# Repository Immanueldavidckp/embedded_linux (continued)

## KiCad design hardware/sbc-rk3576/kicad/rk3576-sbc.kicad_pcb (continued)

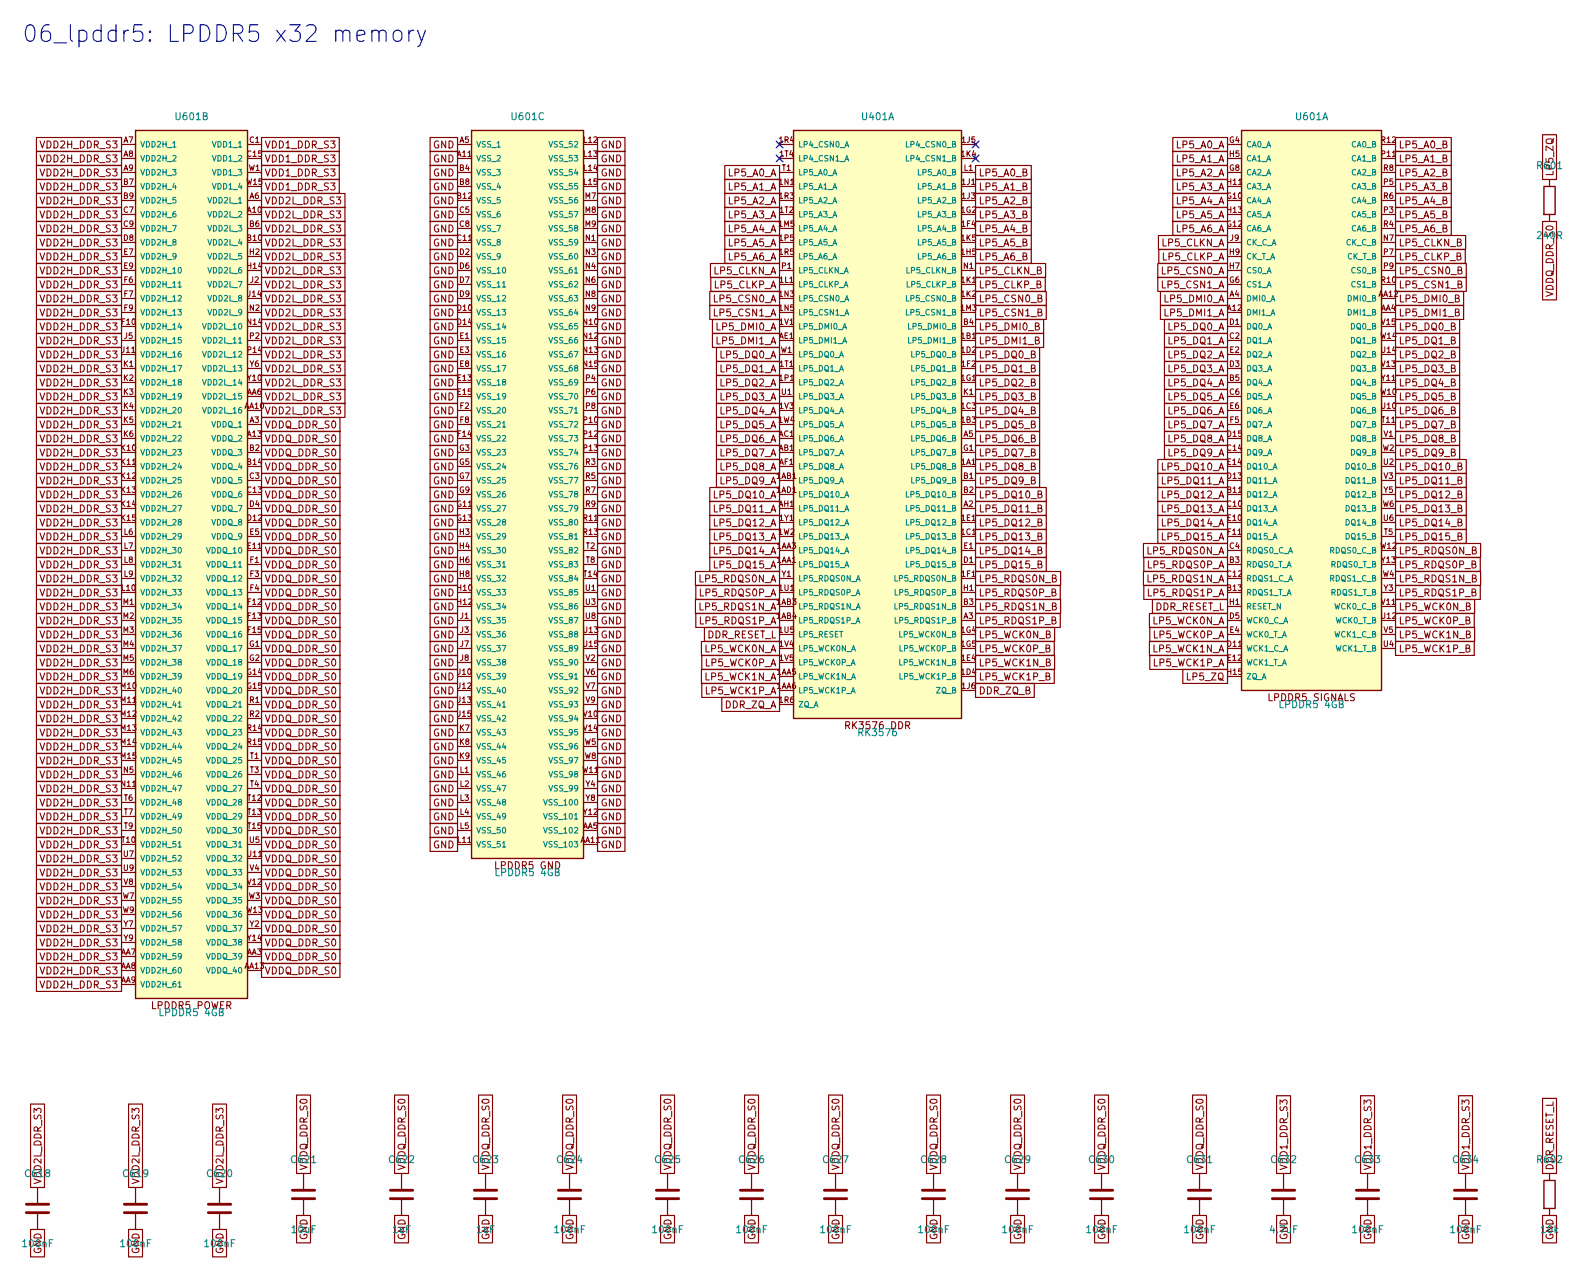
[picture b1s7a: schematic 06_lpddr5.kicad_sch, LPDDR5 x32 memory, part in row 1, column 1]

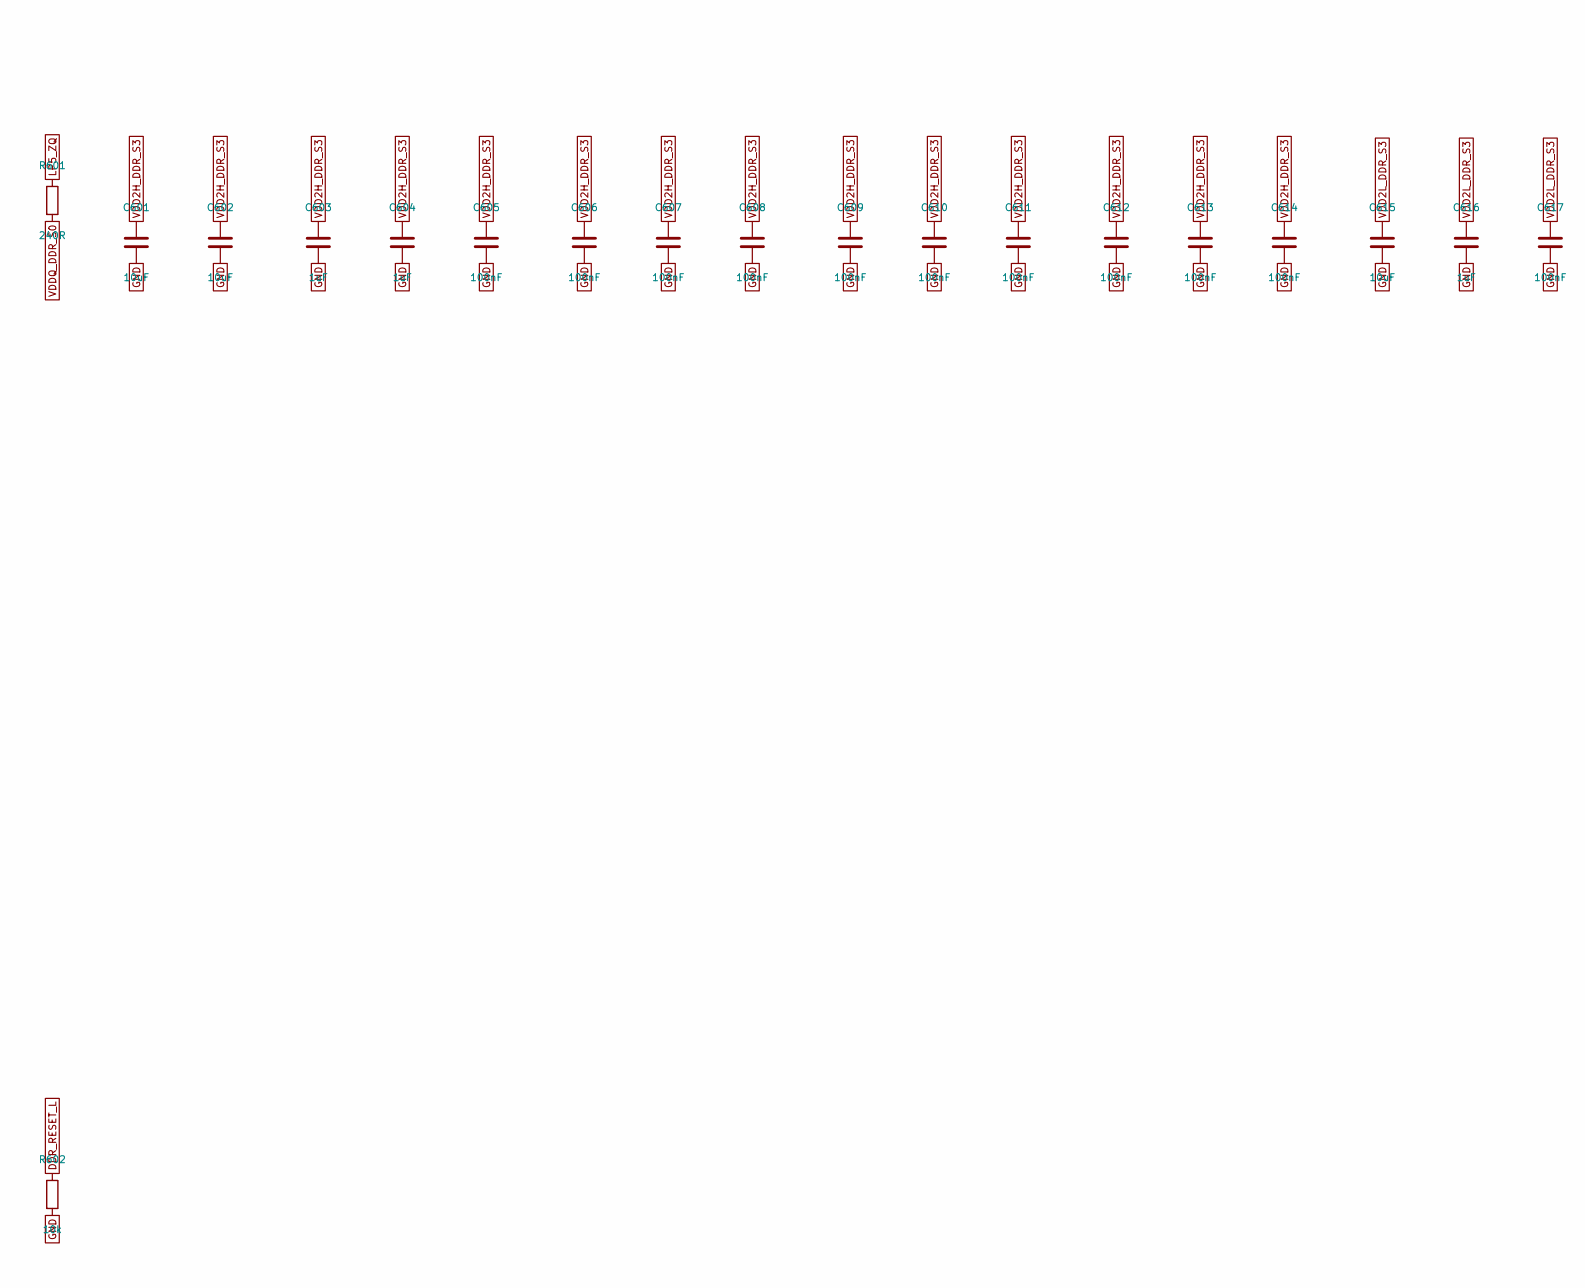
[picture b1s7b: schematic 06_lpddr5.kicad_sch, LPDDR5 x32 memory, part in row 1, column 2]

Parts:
C601, C602, C615, C621: 10uF; C_0603_1608Metric; MPN 0603 10uF 10V X5R
C603, C604, C616, C622, C623: 1uF; C_0402_1005Metric; MPN 0402 1uF 6.3V X5R
C605, C606, C607, C608, C609, C610, C611, C612, C613, C614, C617, C618, C619, C620, C624, C625, C626, C627, C628, C629, C630, C631, C633, C634: 100nF; C_0402_1005Metric; MPN 0402 100nF 6.3V X5R
C632: 4.7uF; C_0402_1005Metric; MPN 0402 4.7uF 10V X5R
R601: 240R; R_0402_1005Metric; MPN 0402 240R 1%
R602: 10k; R_0402_1005Metric; MPN 0402 10k 1%
U401: RK3576; RK3576_FCCSP-698_16.1x17.2mm; MPN RK3576
U601: LPDDR5 4GB; LPDDR5_FBGA-315_12.4x15.0mm_P0.8x0.7mm; MPN MT62F1G32D2DS-026 WT:B (4GB) | alt MT62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

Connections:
DDR_RESET_L: R602.1, U401.1U5 (LP5_RESET), U601.H1 (RESET_N)
DDR_ZQ_A: U401.1R6 (ZQ_A); also elsewhere on the board
DDR_ZQ_B: U401.1J6 (ZQ_B); also elsewhere on the board
GND: C601.2, C602.2, C603.2, C604.2, C605.2, C606.2, C607.2, C608.2, C609.2, C610.2, C611.2, C612.2, C613.2, C614.2, C615.2, C616.2, C617.2, C618.2, C619.2, C620.2, C621.2, C622.2, C623.2, C624.2, C625.2, C626.2, C627.2, C628.2, C629.2, C630.2, C631.2, C632.2, C633.2, C634.2, R602.2, U601.A5 (VSS_1), U601.A11 (VSS_2), U601.AA5 (VSS_102), U601.AA11 (VSS_103), U601.B4 (VSS_3), U601.B8 (VSS_4), U601.B12 (VSS_5), U601.C5 (VSS_6), U601.C8 (VSS_7), U601.C11 (VSS_8), U601.D2 (VSS_9), U601.D6 (VSS_10), U601.D7 (VSS_11), U601.D9 (VSS_12), U601.D10 (VSS_13), U601.D14 (VSS_14), U601.E1 (VSS_15), U601.E3 (VSS_16), U601.E8 (VSS_17), U601.E13 (VSS_18), U601.E15 (VSS_19), U601.F2 (VSS_20), U601.F8 (VSS_21), U601.F14 (VSS_22), U601.G3 (VSS_23), U601.G5 (VSS_24), U601.G7 (VSS_25), U601.G9 (VSS_26), U601.G11 (VSS_27), U601.G13 (VSS_28), U601.H3 (VSS_29), U601.H4 (VSS_30), U601.H6 (VSS_31), U601.H8 (VSS_32), U601.H10 (VSS_33), U601.H12 (VSS_34), U601.J1 (VSS_35), U601.J3 (VSS_36), U601.J7 (VSS_37), U601.J8 (VSS_38), U601.J10 (VSS_39), U601.J12 (VSS_40), U601.J13 (VSS_41), U601.J15 (VSS_42), U601.K7 (VSS_43), U601.K8 (VSS_44), U601.K9 (VSS_45), U601.L1 (VSS_46), U601.L2 (VSS_47), U601.L3 (VSS_48), U601.L4 (VSS_49), U601.L5 (VSS_50), U601.L11 (VSS_51), U601.L12 (VSS_52), U601.L13 (VSS_53), U601.L14 (VSS_54), U601.L15 (VSS_55), U601.M7 (VSS_56), U601.M8 (VSS_57), U601.M9 (VSS_58), U601.N1 (VSS_59), U601.N3 (VSS_60), U601.N4 (VSS_61), U601.N6 (VSS_62), U601.N8 (VSS_63), U601.N9 (VSS_64), U601.N10 (VSS_65), U601.N12 (VSS_66), U601.N13 (VSS_67), U601.N15 (VSS_68), U601.P4 (VSS_69), U601.P6 (VSS_70), U601.P8 (VSS_71), U601.P10 (VSS_72), U601.P12 (VSS_73), U601.P13 (VSS_74), U601.R3 (VSS_76), U601.R5 (VSS_77), U601.R7 (VSS_78), U601.R9 (VSS_79), U601.R11 (VSS_80), U601.R13 (VSS_81), U601.T2 (VSS_82), U601.T8 (VSS_83), U601.T14 (VSS_84), U601.U1 (VSS_85), U601.U3 (VSS_86), U601.U8 (VSS_87), U601.U13 (VSS_88), U601.U15 (VSS_89), U601.V2 (VSS_90), U601.V6 (VSS_91), U601.V7 (VSS_92), U601.V9 (VSS_93), U601.V10 (VSS_94), U601.V14 (VSS_95), U601.W5 (VSS_96), U601.W8 (VSS_97), U601.W11 (VSS_98), U601.Y4 (VSS_99), U601.Y8 (VSS_100), U601.Y12 (VSS_101); also elsewhere on the board
LP5_A0_A: U401.T1 (LP5_A0_A), U601.G4 (CA0_A)
LP5_A0_B: U401.L1 (LP5_A0_B), U601.R12 (CA0_B)
LP5_A1_A: U401.1N1 (LP5_A1_A), U601.H5 (CA1_A)
LP5_A1_B: U401.1J1 (LP5_A1_B), U601.P11 (CA1_B)
LP5_A2_A: U401.1R3 (LP5_A2_A), U601.G8 (CA2_A)
LP5_A2_B: U401.1J3 (LP5_A2_B), U601.R8 (CA2_B)
LP5_A3_A: U401.1T2 (LP5_A3_A), U601.H11 (CA3_A)
LP5_A3_B: U401.1G2 (LP5_A3_B), U601.P5 (CA3_B)
LP5_A4_A: U401.1M5 (LP5_A4_A), U601.G10 (CA4_A)
LP5_A4_B: U401.1F4 (LP5_A4_B), U601.R6 (CA4_B)
LP5_A5_A: U401.1P5 (LP5_A5_A), U601.H13 (CA5_A)
LP5_A5_B: U401.1K5 (LP5_A5_B), U601.P3 (CA5_B)
LP5_A6_A: U401.1R5 (LP5_A6_A), U601.G12 (CA6_A)
LP5_A6_B: U401.1H5 (LP5_A6_B), U601.R4 (CA6_B)
LP5_CLKN_A: U401.P1 (LP5_CLKN_A), U601.J9 (CK_C_A)
LP5_CLKN_B: U401.N1 (LP5_CLKN_B), U601.N7 (CK_C_B)
LP5_CLKP_A: U401.1L1 (LP5_CLKP_A), U601.H9 (CK_T_A)
LP5_CLKP_B: U401.1K1 (LP5_CLKP_B), U601.P7 (CK_T_B)
LP5_CSN0_A: U401.1N3 (LP5_CSN0_A), U601.H7 (CS0_A)
LP5_CSN0_B: U401.1K2 (LP5_CSN0_B), U601.P9 (CS0_B)
LP5_CSN1_A: U401.1N5 (LP5_CSN1_A), U601.G6 (CS1_A)
LP5_CSN1_B: U401.1M3 (LP5_CSN1_B), U601.R10 (CS1_B)
LP5_DMI0_A: U401.1V1 (LP5_DMI0_A), U601.A4 (DMI0_A)
LP5_DMI0_B: U401.B4 (LP5_DMI0_B), U601.AA12 (DMI0_B)
LP5_DMI1_A: U401.AE1 (LP5_DMI1_A), U601.A12 (DMI1_A)
LP5_DMI1_B: U401.1B1 (LP5_DMI1_B), U601.AA4 (DMI1_B)
LP5_DQ0_A: U401.W1 (LP5_DQ0_A), U601.D1 (DQ0_A)
LP5_DQ0_B: U401.1D2 (LP5_DQ0_B), U601.V15 (DQ0_B)
LP5_DQ1_A: U401.1T1 (LP5_DQ1_A), U601.C2 (DQ1_A)
LP5_DQ1_B: U401.1F2 (LP5_DQ1_B), U601.W14 (DQ1_B)
LP5_DQ2_A: U401.1P1 (LP5_DQ2_A), U601.E2 (DQ2_A)
LP5_DQ2_B: U401.1G1 (LP5_DQ2_B), U601.U14 (DQ2_B)
LP5_DQ3_A: U401.U1 (LP5_DQ3_A), U601.D3 (DQ3_A)
LP5_DQ3_B: U401.K1 (LP5_DQ3_B), U601.V13 (DQ3_B)
LP5_DQ4_A: U401.1V3 (LP5_DQ4_A), U601.B5 (DQ4_A)
LP5_DQ4_B: U401.1C3 (LP5_DQ4_B), U601.Y11 (DQ4_B)
LP5_DQ5_A: U401.1W4 (LP5_DQ5_A), U601.C6 (DQ5_A)
LP5_DQ5_B: U401.1B3 (LP5_DQ5_B), U601.W10 (DQ5_B)
LP5_DQ6_A: U401.AC1 (LP5_DQ6_A), U601.E6 (DQ6_A)
LP5_DQ6_B: U401.A5 (LP5_DQ6_B), U601.U10 (DQ6_B)
LP5_DQ7_A: U401.AB1 (LP5_DQ7_A), U601.F5 (DQ7_A)
LP5_DQ7_B: U401.G1 (LP5_DQ7_B), U601.T11 (DQ7_B)
LP5_DQ8_A: U401.AF1 (LP5_DQ8_A), U601.D15 (DQ8_A)
LP5_DQ8_B: U401.1A1 (LP5_DQ8_B), U601.V1 (DQ8_B)
LP5_DQ9_A: U401.1AB1 (LP5_DQ9_A), U601.C14 (DQ9_A)
LP5_DQ9_B: U401.B1 (LP5_DQ9_B), U601.W2 (DQ9_B)
LP5_DQ10_A: U401.1AD1 (LP5_DQ10_A), U601.E14 (DQ10_A)
LP5_DQ10_B: U401.B2 (LP5_DQ10_B), U601.U2 (DQ10_B)
LP5_DQ11_A: U401.AH1 (LP5_DQ11_A), U601.D13 (DQ11_A)
LP5_DQ11_B: U401.A2 (LP5_DQ11_B), U601.V3 (DQ11_B)
LP5_DQ12_A: U401.1Y1 (LP5_DQ12_A), U601.B11 (DQ12_A)
LP5_DQ12_B: U401.1E1 (LP5_DQ12_B), U601.Y5 (DQ12_B)
LP5_DQ13_A: U401.1W2 (LP5_DQ13_A), U601.C10 (DQ13_A)
LP5_DQ13_B: U401.1C1 (LP5_DQ13_B), U601.W6 (DQ13_B)
LP5_DQ14_A: U401.1AA3 (LP5_DQ14_A), U601.E10 (DQ14_A)
LP5_DQ14_B: U401.E1 (LP5_DQ14_B), U601.U6 (DQ14_B)
LP5_DQ15_A: U401.1AA1 (LP5_DQ15_A), U601.F11 (DQ15_A)
LP5_DQ15_B: U401.D1 (LP5_DQ15_B), U601.T5 (DQ15_B)
LP5_RDQS0N_A: U401.Y1 (LP5_RDQS0N_A), U601.C4 (RDQS0_C_A)
LP5_RDQS0N_B: U401.1F1 (LP5_RDQS0N_B), U601.W12 (RDQS0_C_B)
LP5_RDQS0P_A: U401.1U1 (LP5_RDQS0P_A), U601.B3 (RDQS0_T_A)
LP5_RDQS0P_B: U401.H1 (LP5_RDQS0P_B), U601.Y13 (RDQS0_T_B)
LP5_RDQS1N_A: U401.1AB3 (LP5_RDQS1N_A), U601.C12 (RDQS1_C_A)
LP5_RDQS1N_B: U401.B3 (LP5_RDQS1N_B), U601.W4 (RDQS1_C_B)
LP5_RDQS1P_A: U401.1AB4 (LP5_RDQS1P_A), U601.B13 (RDQS1_T_A)
LP5_RDQS1P_B: U401.A3 (LP5_RDQS1P_B), U601.Y3 (RDQS1_T_B)
LP5_WCK0N_A: U401.1V4 (LP5_WCK0N_A), U601.D5 (WCK0_C_A)
LP5_WCK0N_B: U401.1G4 (LP5_WCK0N_B), U601.V11 (WCK0_C_B)
LP5_WCK0P_A: U401.1V5 (LP5_WCK0P_A), U601.E4 (WCK0_T_A)
LP5_WCK0P_B: U401.1G5 (LP5_WCK0P_B), U601.U12 (WCK0_T_B)
LP5_WCK1N_A: U401.1AA5 (LP5_WCK1N_A), U601.D11 (WCK1_C_A)
LP5_WCK1N_B: U401.1E4 (LP5_WCK1N_B), U601.V5 (WCK1_C_B)
LP5_WCK1P_A: U401.1AA6 (LP5_WCK1P_A), U601.E12 (WCK1_T_A)
LP5_WCK1P_B: U401.1D4 (LP5_WCK1P_B), U601.U4 (WCK1_T_B)
LP5_ZQ: R601.1, U601.H15 (ZQ_A)
VDD1_DDR_S3: C632.1, C633.1, C634.1, U601.C1 (VDD1_1), U601.C15 (VDD1_2), U601.W1 (VDD1_3), U601.W15 (VDD1_4); also elsewhere on the board
VDD2H_DDR_S3: C601.1, C602.1, C603.1, C604.1, C605.1, C606.1, C607.1, C608.1, C609.1, C610.1, C611.1, C612.1, C613.1, C614.1, U601.A7 (VDD2H_1), U601.A8 (VDD2H_2), U601.A9 (VDD2H_3), U601.AA7 (VDD2H_59), U601.AA8 (VDD2H_60), U601.AA9 (VDD2H_61), U601.B7 (VDD2H_4), U601.B9 (VDD2H_5), U601.C7 (VDD2H_6), U601.C9 (VDD2H_7), U601.D8 (VDD2H_8), U601.E7 (VDD2H_9), U601.E9 (VDD2H_10), U601.F6 (VDD2H_11), U601.F7 (VDD2H_12), U601.F9 (VDD2H_13), U601.F10 (VDD2H_14), U601.J5 (VDD2H_15), U601.J11 (VDD2H_16), U601.K1 (VDD2H_17), U601.K2 (VDD2H_18), U601.K3 (VDD2H_19), U601.K4 (VDD2H_20), U601.K5 (VDD2H_21), U601.K6 (VDD2H_22), U601.K10 (VDD2H_23), U601.K11 (VDD2H_24), U601.K12 (VDD2H_25), U601.K13 (VDD2H_26), U601.K14 (VDD2H_27), U601.K15 (VDD2H_28), U601.L6 (VDD2H_29), U601.L7 (VDD2H_30), U601.L8 (VDD2H_31), U601.L9 (VDD2H_32), U601.L10 (VDD2H_33), U601.M1 (VDD2H_34), U601.M2 (VDD2H_35), U601.M3 (VDD2H_36), U601.M4 (VDD2H_37), U601.M5 (VDD2H_38), U601.M6 (VDD2H_39), U601.M10 (VDD2H_40), U601.M11 (VDD2H_41), U601.M12 (VDD2H_42), U601.M13 (VDD2H_43), U601.M14 (VDD2H_44), U601.M15 (VDD2H_45), U601.N5 (VDD2H_46), U601.N11 (VDD2H_47), U601.T6 (VDD2H_48), U601.T7 (VDD2H_49), U601.T9 (VDD2H_50), U601.T10 (VDD2H_51), U601.U7 (VDD2H_52), U601.U9 (VDD2H_53), U601.V8 (VDD2H_54), U601.W7 (VDD2H_55), U601.W9 (VDD2H_56), U601.Y7 (VDD2H_57), U601.Y9 (VDD2H_58); also elsewhere on the board
VDD2L_DDR_S3: C615.1, C616.1, C617.1, C618.1, C619.1, C620.1, U601.A6 (VDD2L_1), U601.A10 (VDD2L_2), U601.AA6 (VDD2L_15), U601.AA10 (VDD2L_16), U601.B6 (VDD2L_3), U601.B10 (VDD2L_4), U601.H2 (VDD2L_5), U601.H14 (VDD2L_6), U601.J2 (VDD2L_7), U601.J14 (VDD2L_8), U601.N2 (VDD2L_9), U601.N14 (VDD2L_10), U601.P2 (VDD2L_11), U601.P14 (VDD2L_12), U601.Y6 (VDD2L_13), U601.Y10 (VDD2L_14); also elsewhere on the board
VDDQ_DDR_S0: C621.1, C622.1, C623.1, C624.1, C625.1, C626.1, C627.1, C628.1, C629.1, C630.1, C631.1, R601.2, U601.A3 (VDDQ_1), U601.A13 (VDDQ_2), U601.AA3 (VDDQ_39), U601.AA13 (VDDQ_40), U601.B2 (VDDQ_3), U601.B14 (VDDQ_4), U601.C3 (VDDQ_5), U601.C13 (VDDQ_6), U601.D4 (VDDQ_7), U601.D12 (VDDQ_8), U601.E5 (VDDQ_9), U601.E11 (VDDQ_10), U601.F1 (VDDQ_11), U601.F3 (VDDQ_12), U601.F4 (VDDQ_13), U601.F12 (VDDQ_14), U601.F13 (VDDQ_15), U601.F15 (VDDQ_16), U601.G1 (VDDQ_17), U601.G2 (VDDQ_18), U601.G14 (VDDQ_19), U601.G15 (VDDQ_20), U601.R1 (VDDQ_21), U601.R2 (VDDQ_22), U601.R14 (VDDQ_23), U601.R15 (VDDQ_24), U601.T1 (VDDQ_25), U601.T3 (VDDQ_26), U601.T4 (VDDQ_27), U601.T12 (VDDQ_28), U601.T13 (VDDQ_29), U601.T15 (VDDQ_30), U601.U5 (VDDQ_31), U601.U11 (VDDQ_32), U601.V4 (VDDQ_33), U601.V12 (VDDQ_34), U601.W3 (VDDQ_35), U601.W13 (VDDQ_36), U601.Y2 (VDDQ_37), U601.Y14 (VDDQ_38); also elsewhere on the board

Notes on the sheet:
06_lpddr5: LPDDR5 x32 memory

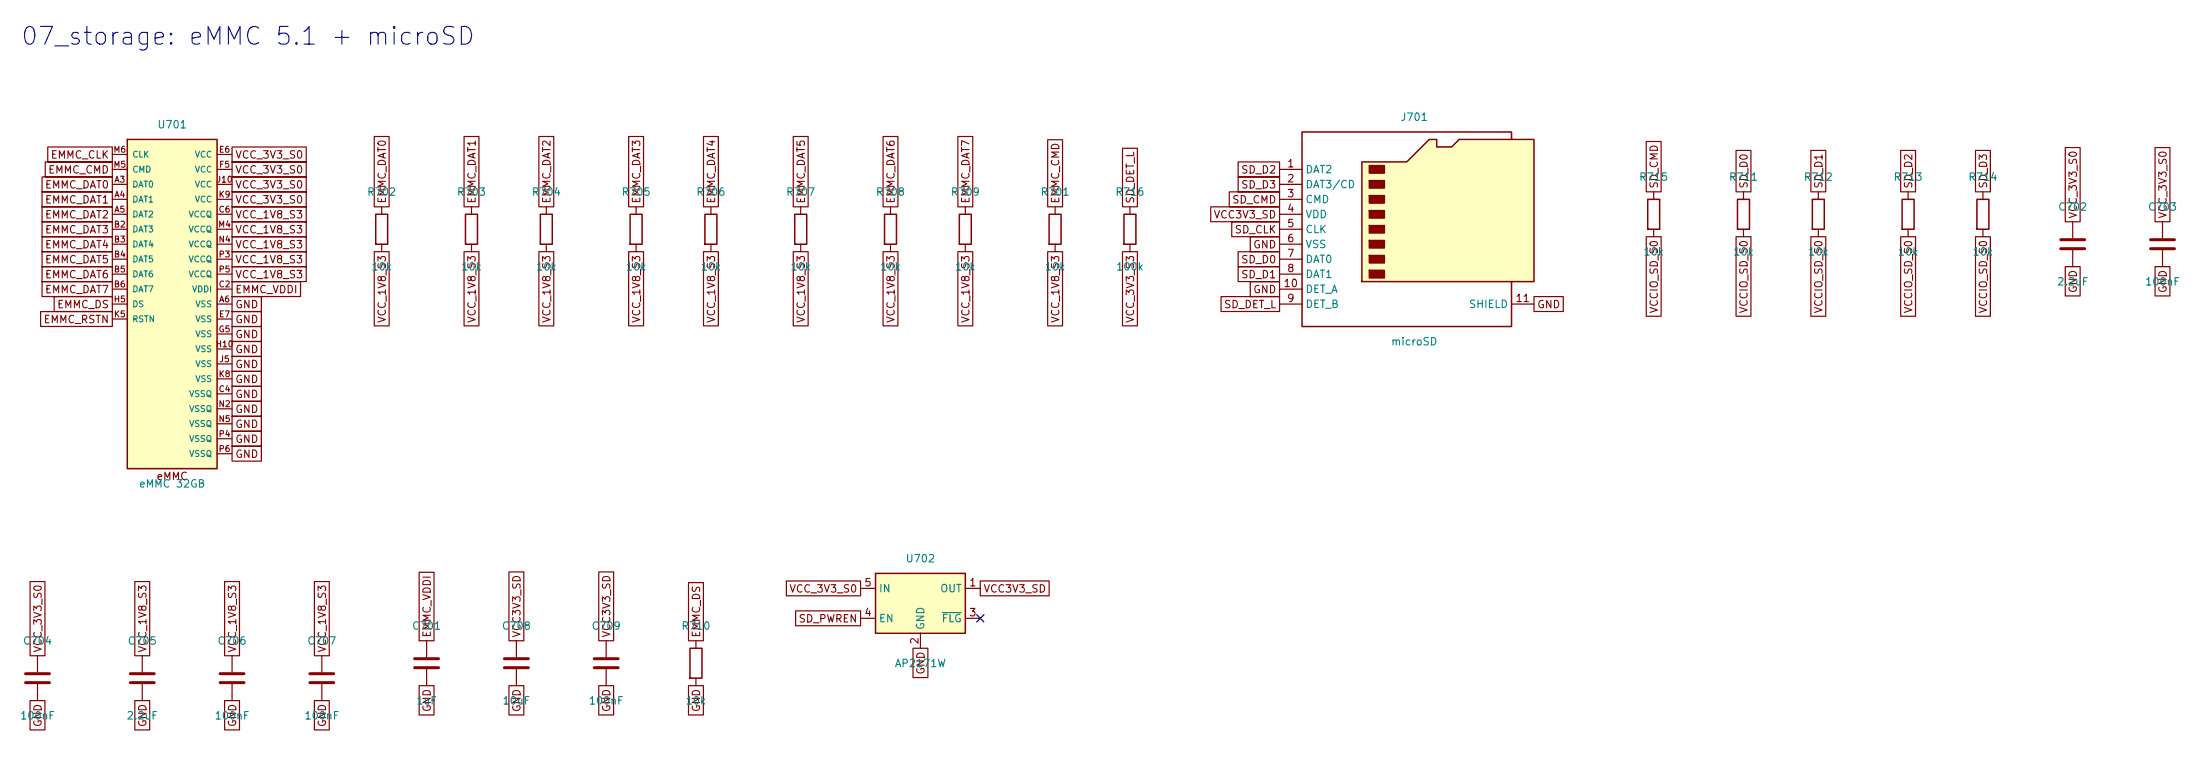
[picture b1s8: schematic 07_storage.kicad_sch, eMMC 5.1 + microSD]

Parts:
C701: 1uF; C_0402_1005Metric; MPN 0402 1uF 6.3V X5R
C702, C705: 2.2uF; C_0402_1005Metric; MPN 0402 2.2uF 6.3V X5R
C703, C704, C706, C707, C709: 100nF; C_0402_1005Metric; MPN 0402 100nF 6.3V X5R
C708: 10uF; C_0603_1608Metric; MPN 0603 10uF 10V X5R
J701: microSD; microSD_HC_Hirose_DM3AT-SF-PEJM5; MPN DM3AT-SF-PEJM5
R701, R710, R711, R712, R713, R714, R715: 10k; R_0402_1005Metric; MPN 0402 10k 1%
R702, R703, R704, R705, R706, R707, R708, R709: 10k; R_0201_0603Metric; MPN 0201 10k 1%
R716: 100k; R_0402_1005Metric; MPN 0402 100k 1%
U701: eMMC 32GB; eMMC_FBGA-153_11.5x13.0mm_P0.5mm; MPN FEMDNN032G-A3A55 (32GB) | alt KLMBG2JET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
U702: AP2171W; SOT-23-5; MPN AP2171WG-7; LCSC C155555

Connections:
EMMC_CLK: U701.M6 (CLK); also elsewhere on the board
EMMC_CMD: R701.1, U701.M5 (CMD); also elsewhere on the board
EMMC_DAT0: R702.1, U701.A3 (DAT0); also elsewhere on the board
EMMC_DAT1: R703.1, U701.A4 (DAT1); also elsewhere on the board
EMMC_DAT2: R704.1, U701.A5 (DAT2); also elsewhere on the board
EMMC_DAT3: R705.1, U701.B2 (DAT3); also elsewhere on the board
EMMC_DAT4: R706.1, U701.B3 (DAT4); also elsewhere on the board
EMMC_DAT5: R707.1, U701.B4 (DAT5); also elsewhere on the board
EMMC_DAT6: R708.1, U701.B5 (DAT6); also elsewhere on the board
EMMC_DAT7: R709.1, U701.B6 (DAT7); also elsewhere on the board
EMMC_DS: R710.1, U701.H5 (DS); also elsewhere on the board
EMMC_RSTN: U701.K5 (RSTN); also elsewhere on the board
EMMC_VDDI: C701.1, U701.C2 (VDDI)
GND: C701.2, C702.2, C703.2, C704.2, C705.2, C706.2, C707.2, C708.2, C709.2, J701.6 (VSS), J701.10 (DET_A), J701.11 (SHIELD), R710.2, U701.A6 (VSS), U701.C4 (VSSQ), U701.E7 (VSS), U701.G5 (VSS), U701.H10 (VSS), U701.J5 (VSS), U701.K8 (VSS), U701.N2 (VSSQ), U701.N5 (VSSQ), U701.P4 (VSSQ), U701.P6 (VSSQ), U702.2 (GND); also elsewhere on the board
SD_CLK: J701.5 (CLK); also elsewhere on the board
SD_CMD: J701.3 (CMD), R715.1; also elsewhere on the board
SD_D0: J701.7 (DAT0), R711.1; also elsewhere on the board
SD_D1: J701.8 (DAT1), R712.1; also elsewhere on the board
SD_D2: J701.1 (DAT2), R713.1; also elsewhere on the board
SD_D3: J701.2 (DAT3/CD), R714.1; also elsewhere on the board
SD_DET_L: J701.9 (DET_B), R716.1; also elsewhere on the board
SD_PWREN: U702.4 (EN); also elsewhere on the board
VCC3V3_SD: C708.1, C709.1, J701.4 (VDD), U702.1 (OUT)
VCCIO_SD_S0: R711.2, R712.2, R713.2, R714.2, R715.2; also elsewhere on the board
VCC_1V8_S3: C705.1, C706.1, C707.1, R701.2, R702.2, R703.2, R704.2, R705.2, R706.2, R707.2, R708.2, R709.2, U701.C6 (VCCQ), U701.M4 (VCCQ), U701.N4 (VCCQ), U701.P3 (VCCQ), U701.P5 (VCCQ); also elsewhere on the board
VCC_3V3_S0: C702.1, C703.1, C704.1, U701.E6 (VCC), U701.F5 (VCC), U701.J10 (VCC), U701.K9 (VCC), U702.5 (IN); also elsewhere on the board
VCC_3V3_S3: R716.2; also elsewhere on the board

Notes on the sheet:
07_storage: eMMC 5.1 + microSD

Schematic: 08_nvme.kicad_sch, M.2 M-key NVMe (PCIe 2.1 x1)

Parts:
C801, C802: 220nF; C_0201_0603Metric; MPN 0201 220nF 6.3V X5R
C803, C804: 22uF; C_0603_1608Metric; MPN 0603 22uF 10V X5R
C805, C806: 100nF; C_0402_1005Metric; MPN 0402 100nF 6.3V X5R
H801: M2 standoff 2242; SMD_Standoff_M2_D4.0mm; MPN 9774020243R (M2 SMD standoff)
H802: M2 standoff 2230; SMD_Standoff_M2_D4.0mm; MPN 9774020243R (M2 SMD standoff)
J801: M.2 M-KEY; M.2_Socket3_M-Key_H4.2mm; MPN APCI0026-P001A (M.2 M key, H4.2)
LED801: SSD; LED_0603_1608Metric; MPN 19-217/GHC-YR1S2/3T; LCSC C72043
R801, R802, R803: 10k; R_0402_1005Metric; MPN 0402 10k 1%
R804: 1k; R_0402_1005Metric; MPN 0402 1k 1%

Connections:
GND: C803.2, C804.2, C805.2, C806.2, H801.1, H802.1, J801.1 (GND), J801.3 (GND), J801.9 (GND), J801.15 (GND), J801.21 (GND), J801.27 (GND), J801.33 (GND), J801.39 (GND), J801.45 (GND), J801.51 (GND), J801.57 (GND), J801.71 (GND), J801.73 (GND), J801.75 (GND), R803.2; also elsewhere on the board
M2_LED_A: LED801.2 (A), R804.1
M2_LED_L: J801.10 (LED1#), LED801.1 (K)
M2_PETN0: C802.2, J801.47 (PETn0)
M2_PETP0: C801.2, J801.49 (PETp0)
PCIE0_CLKREQ_L: J801.52 (CLKREQ#), R801.1; also elsewhere on the board
PCIE0_PERST_L: J801.50 (PERST#), R803.1; also elsewhere on the board
PCIE0_REFCLKN: J801.53 (REFCLKn); also elsewhere on the board
PCIE0_REFCLKP: J801.55 (REFCLKp); also elsewhere on the board
PCIE0_RXN: J801.41 (PERn0); also elsewhere on the board
PCIE0_RXP: J801.43 (PERp0); also elsewhere on the board
PCIE0_TXN: C802.1; also elsewhere on the board
PCIE0_TXP: C801.1; also elsewhere on the board
PCIE0_WAKE_L: J801.54 (PEWAKE#), R802.1; also elsewhere on the board
VCC3V3_PCIE: C803.1, C804.1, C805.1, C806.1, J801.2 (3V3), J801.4 (3V3), J801.12 (3V3), J801.14 (3V3), J801.16 (3V3), J801.18 (3V3), J801.70 (3V3), J801.72 (3V3), J801.74 (3V3), R804.2; also elsewhere on the board
VCC_3V3_S0: R801.2, R802.2; also elsewhere on the board

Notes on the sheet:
08_nvme: M.2 M-key NVMe (PCIe 2.1 x1)

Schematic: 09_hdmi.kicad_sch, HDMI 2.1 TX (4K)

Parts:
C901, C902, C903, C904, C905, C906, C907, C908: 220nF; C_0201_0603Metric; MPN 0201 220nF 6.3V X5R
C909: 1uF; C_0402_1005Metric; MPN 0402 1uF 10V X5R
C910: 100nF; C_0402_1005Metric; MPN 0402 100nF 10V X5R
D901: B5819W; D_SOD-123; MPN B5819W; LCSC C8598
F901: 0.5A PTC; Fuse_1206_3216Metric; MPN 1206L050/15YR
J901: HDMI; HDMI_A_Molex_208658-1001_Horizontal; MPN 208658-1001
Q901, Q902, Q903, Q904, Q905, Q906, Q907: BSS138; SOT-23; MPN BSS138; LCSC C52895
R901, R902, R903, R904, R905, R906, R907, R908: 590R; R_0402_1005Metric; MPN 0402 590R 1%
R909, R911, R913: 4.7k; R_0402_1005Metric; MPN 0402 4.7k 1%
R910, R912: 1.8k; R_0402_1005Metric; MPN 0402 1.8k 1%
R914: 27k; R_0402_1005Metric; MPN 0402 27k 1%
R915: 10k; R_0402_1005Metric; MPN 0402 10k 1%
R916: 20k; R_0402_1005Metric; MPN 0402 20k 1%
R917: 100k; R_0402_1005Metric; MPN 0402 100k 1%
U901, U902: TPD4E05U06; USON-10_2.5x1.0mm_P0.5mm; MPN TPD4E05U06DQAR

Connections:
GND: C909.2, C910.2, J901.2 (D2S), J901.5 (D1S), J901.8 (D0S), J901.11 (CKS), J901.17 (GND), J901.SH, Q901.2 (S), Q902.2 (S), Q903.2 (S), Q904.2 (S), R916.2, R917.2, U901.3 (GND), U901.8 (GND), U902.3 (GND), U902.8 (GND); also elsewhere on the board
HDMI_5V_PTC: D901.1 (K), F901.1
HDMI_CEC: Q907.2 (S), R913.1; also elsewhere on the board
HDMI_CEC_5V: J901.13 (CEC), Q907.3 (D), R914.1
HDMI_D0N_C: C902.2, J901.9 (D0-), R902.1, U902.2 (D1-)
HDMI_D0P_C: C901.2, J901.7 (D0+), R901.1, U902.1 (D1+)
HDMI_D0_TERM: Q901.3 (D), R901.2, R902.2
HDMI_D1N_C: C904.2, J901.6 (D1-), R904.1, U901.5 (D2-)
HDMI_D1P_C: C903.2, J901.4 (D1+), R903.1, U901.4 (D2+)
HDMI_D1_TERM: Q902.3 (D), R903.2, R904.2
HDMI_D2N_C: C906.2, J901.3 (D2-), R906.1, U901.2 (D1-)
HDMI_D2P_C: C905.2, J901.1 (D2+), R905.1, U901.1 (D1+)
HDMI_D2_TERM: Q903.3 (D), R905.2, R906.2
HDMI_D3N_C: C908.2, J901.12 (CK-), R908.1, U902.5 (D2-)
HDMI_D3P_C: C907.2, J901.10 (CK+), R907.1, U902.4 (D2+)
HDMI_D3_TERM: Q904.3 (D), R907.2, R908.2
HDMI_HPD: R915.2, R916.1; also elsewhere on the board
HDMI_HPD_5V: J901.19 (HPD), R915.1, R917.1
HDMI_SCL: Q905.2 (S), R909.1; also elsewhere on the board
HDMI_SCL_5V: J901.15 (SCL), Q905.3 (D), R910.1
HDMI_SDA: Q906.2 (S), R911.1; also elsewhere on the board
HDMI_SDA_5V: J901.16 (SDA), Q906.3 (D), R912.1
HDMI_TX_D0N: C902.1; also elsewhere on the board
HDMI_TX_D0P: C901.1; also elsewhere on the board
HDMI_TX_D1N: C904.1; also elsewhere on the board
HDMI_TX_D1P: C903.1; also elsewhere on the board
HDMI_TX_D2N: C906.1; also elsewhere on the board
HDMI_TX_D2P: C905.1; also elsewhere on the board
HDMI_TX_D3N: C908.1; also elsewhere on the board
HDMI_TX_D3P: C907.1; also elsewhere on the board
HDMI_TX_ON_H: Q901.1 (G), Q902.1 (G), Q903.1 (G), Q904.1 (G); also elsewhere on the board
VCC5V0_SYS_S5: D901.2 (A); also elsewhere on the board
VCC5V_HDMI: C909.1, C910.1, F901.2, J901.18 (+5V), R910.2, R912.2
VCC_3V3_S0: Q905.1 (G), Q906.1 (G), Q907.1 (G), R909.2, R911.2, R913.2, R914.2; also elsewhere on the board

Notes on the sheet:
09_hdmi: HDMI 2.1 TX (4K)

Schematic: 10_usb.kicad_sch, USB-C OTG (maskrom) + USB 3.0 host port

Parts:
C1001, C1002: 100nF; C_0201_0603Metric; MPN 0201 100nF 6.3V X5R
C1003: 47uF; C_0805_2012Metric; MPN 0805 47uF 10V X5R
C1004: 100nF; C_0402_1005Metric; MPN 0402 100nF 10V X5R
J1001: USB3.0 A; USB3_A_Molex_48393-001; MPN 48393-0001
R1001: 56k; R_0402_1005Metric; MPN 0402 56k 1%
R1002, R1004: 100k; R_0402_1005Metric; MPN 0402 100k 1%
R1003: 10k; R_0402_1005Metric; MPN 0402 10k 1%
U1001, U1003: USBLC6-2SC6; SOT-23-6; MPN USBLC6-2SC6; LCSC C7519
U1002: TPD4E05U06; USON-10_2.5x1.0mm_P0.5mm; MPN TPD4E05U06DQAR
U1004: AP2171W; SOT-23-5; MPN AP2171WG-7 (1.5A limit); LCSC C155555

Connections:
GND: C1003.2, C1004.2, J1001.4 (GND), J1001.7 (DRAIN), J1001.10 (SHIELD), R1002.2, R1004.2, U1001.2 (GND), U1002.3 (GND), U1002.8 (GND), U1003.2 (GND), U1004.2 (GND); also elsewhere on the board
USB3A_DM: J1001.2 (D-), U1003.3 (I/O2), U1003.4 (I/O2); also elsewhere on the board
USB3A_DP: J1001.3 (D+), U1003.1 (I/O1), U1003.6 (I/O1); also elsewhere on the board
USB3A_OC_L: R1003.1, U1004.3 (~FLG); also elsewhere on the board
USB3A_SSTXN: C1002.2, J1001.8 (SSTX-), U1002.5 (D2-)
USB3A_SSTXP: C1001.2, J1001.9 (SSTX+), U1002.4 (D2+)
USB3_RXN: J1001.5 (SSRX-), U1002.2 (D1-); also elsewhere on the board
USB3_RXP: J1001.6 (SSRX+), U1002.1 (D1+); also elsewhere on the board
USB3_TXN: C1002.1; also elsewhere on the board
USB3_TXP: C1001.1; also elsewhere on the board
USBC_DM: U1001.3 (I/O2), U1001.4 (I/O2); also elsewhere on the board
USBC_DP: U1001.1 (I/O1), U1001.6 (I/O1); also elsewhere on the board
USB_HOST_PWREN: R1004.1, U1004.4 (EN); also elsewhere on the board
USB_OTG0_VBUSDET: R1001.2, R1002.1; also elsewhere on the board
VBUS_IN: R1001.1, U1001.5 (VBUS); also elsewhere on the board
VBUS_USB3A: C1003.1, C1004.1, J1001.1 (VBUS), U1003.5 (VBUS), U1004.1 (OUT); also elsewhere on the board
VCC5V0_SYS_S5: U1004.5 (IN); also elsewhere on the board
VCC_3V3_S3: R1003.2; also elsewhere on the board

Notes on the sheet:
10_usb: USB-C OTG (maskrom) + USB 3.0 host port

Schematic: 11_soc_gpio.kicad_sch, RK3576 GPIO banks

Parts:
U401: RK3576; RK3576_FCCSP-698_16.1x17.2mm; MPN RK3576

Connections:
DBG_UART_RX: U401.AA28 (GPIO0_D5/UART0_RX_M0); also elsewhere on the board
DBG_UART_TX: U401.1U24 (GPIO0_D4/UART0_TX_M0); also elsewhere on the board
EMMC_CLK: U401.1G23 (GPIO1_B1/EMMC_CLK); also elsewhere on the board
EMMC_CMD: U401.1F22 (GPIO1_B0/EMMC_CMD); also elsewhere on the board
EMMC_DAT0: U401.E28 (GPIO1_A0/EMMC_D0); also elsewhere on the board
EMMC_DAT1: U401.E29 (GPIO1_A1/EMMC_D1); also elsewhere on the board
EMMC_DAT2: U401.1C24 (GPIO1_A2/EMMC_D2); also elsewhere on the board
EMMC_DAT3: U401.F28 (GPIO1_A3/EMMC_D3); also elsewhere on the board
EMMC_DAT4: U401.1D24 (GPIO1_A4/EMMC_D4); also elsewhere on the board
EMMC_DAT5: U401.G28 (GPIO1_A5/EMMC_D5); also elsewhere on the board
EMMC_DAT6: U401.D28 (GPIO1_A6/EMMC_D6); also elsewhere on the board
EMMC_DAT7: U401.1B24 (GPIO1_A7/EMMC_D7); also elsewhere on the board
EMMC_DS: U401.1F23 (GPIO1_B2/EMMC_STRB); also elsewhere on the board
EMMC_RSTN: U401.1D23 (GPIO1_B3/EMMC_RSTN); also elsewhere on the board
ETH_MDC: U401.1A7 (GPIO3_A6/VO_LCDC_D21); also elsewhere on the board
ETH_MDIO: U401.A9 (GPIO3_A5/VO_LCDC_D22); also elsewhere on the board
HDMI_CEC: U401.AK3 (GPIO4_C0/DSM_AUD_LP_M1); also elsewhere on the board
HDMI_HPD: U401.AK2 (GPIO4_C1/DSM_AUD_LN_M1); also elsewhere on the board
HDMI_SCL: U401.AL2 (GPIO4_C2/DSM_AUD_RP_M1); also elsewhere on the board
HDMI_SDA: U401.1AE2 (GPIO4_C3/DSM_AUD_RN_M1); also elsewhere on the board
HDMI_TX_ON_H: U401.AK4 (GPIO4_D1/UFS_REFCLK); also elsewhere on the board
LED_SYS_L: U401.1AA22 (GPIO0_C5/SAI0_SDO0_M1); also elsewhere on the board
PCIE0_CLKREQ_L: U401.1AE1 (GPIO4_C6/SAI4_SDI_M2); also elsewhere on the board
PCIE0_PERST_L: U401.AJ1 (GPIO4_C7/SAI4_SCLK_M2); also elsewhere on the board
PCIE0_WAKE_L: U401.AL3 (GPIO4_C4/ISP_PRELIGHT_TRIG_M1); also elsewhere on the board
PHY_INT_L: U401.1D22 (GPIO1_D1/ETH1_RXCTL_M1); also elsewhere on the board
PHY_RST_GPIO: U401.C29 (GPIO1_D0/ETH1_RXD1_M1); also elsewhere on the board
PMIC_INT_L: U401.1T21 (GPIO0_A6/PMIC_INT); also elsewhere on the board
PMIC_PWRCTRL1: U401.Y28 (GPIO0_A3/PWR_CTRL1); also elsewhere on the board
PMIC_PWRCTRL2: U401.1T24 (GPIO0_A4/PWR_CTRL2); also elsewhere on the board
PMIC_PWRCTRL3: U401.Y29 (GPIO0_A5/PWR_CTRL3); also elsewhere on the board
PMIC_SCL: U401.1T22 (GPIO0_B2/SPI2_CLK_M0); also elsewhere on the board
PMIC_SDA: U401.1T23 (GPIO0_B3/SPI2_MOSI_M0); also elsewhere on the board
RGMII_RXC: U401.1A12 (GPIO3_D1/VO_LCDC_D2); also elsewhere on the board
RGMII_RXCTL: U401.B13 (GPIO3_A7/VO_LCDC_D20); also elsewhere on the board
RGMII_RXD0: U401.A13 (GPIO3_B2/VO_LCDC_D17); also elsewhere on the board
RGMII_RXD1: U401.1A11 (GPIO3_B1/VO_LCDC_D18); also elsewhere on the board
RGMII_RXD2: U401.B12 (GPIO3_D3/VO_LCDC_D0); also elsewhere on the board
RGMII_RXD3: U401.1A10 (GPIO3_D2/VO_LCDC_D1); also elsewhere on the board
RGMII_TXCTL: U401.A11 (GPIO3_B3/VO_LCDC_D16); also elsewhere on the board
RGMII_TXC_SOC: U401.B11 (GPIO3_B6/VO_LCDC_D13); also elsewhere on the board
RGMII_TXD0: U401.1A9 (GPIO3_B5/VO_LCDC_D14); also elsewhere on the board
RGMII_TXD1: U401.B10 (GPIO3_B4/VO_LCDC_D15); also elsewhere on the board
RGMII_TXD2: U401.1A8 (GPIO3_C3/VO_LCDC_D8); also elsewhere on the board
RGMII_TXD3: U401.B9 (GPIO3_C2/VO_LCDC_D9); also elsewhere on the board
SD_CLK: U401.1B21 (GPIO2_A5/SDMMC0_CLK); also elsewhere on the board
SD_CMD: U401.1A21 (GPIO2_A4/SDMMC0_CMD); also elsewhere on the board
SD_D0: U401.B24 (GPIO2_A0/SDMMC0_D0); also elsewhere on the board
SD_D1: U401.B25 (GPIO2_A1/SDMMC0_D1); also elsewhere on the board
SD_D2: U401.A23 (GPIO2_A2/SDMMC0_D2); also elsewhere on the board
SD_D3: U401.B23 (GPIO2_A3/SDMMC0_D3); also elsewhere on the board
SD_DET_L: U401.1U21 (GPIO0_A7/SDMMC0_DETN); also elsewhere on the board
SD_PWREN: U401.1Y24 (GPIO0_B6/SDMMC0_PWREN); also elsewhere on the board
USB3A_OC_L: U401.1Y21 (GPIO0_C6/SAI0_SCLK_M1); also elsewhere on the board
USB_HOST_PWREN: U401.1W22 (GPIO0_C4/SAI0_MCLK_M1); also elsewhere on the board
WIFI_PD_GPIO: U401.1A24 (GPIO1_D2/ETH1_MDC_M1); also elsewhere on the board

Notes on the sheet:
11_soc_gpio: RK3576 GPIO banks

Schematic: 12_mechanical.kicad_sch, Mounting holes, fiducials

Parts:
FID1201, FID1202, FID1203: FID; Fiducial_1mm_Mask2mm
H1201, H1202, H1203, H1204: M2.5; MountingHole_2.7mm_M2.5_Pad_Via

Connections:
GND: H1201.1, H1202.1, H1203.1, H1204.1; also elsewhere on the board

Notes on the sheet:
12_mechanical: Mounting holes, fiducials

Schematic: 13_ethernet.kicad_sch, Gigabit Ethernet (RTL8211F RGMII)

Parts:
C1301: 10uF; C_0603_1608Metric; MPN 0603 10uF 10V X5R
C1302, C1303, C1304, C1307, C1308, C1309, C1310, C1315, C1316: 100nF; C_0402_1005Metric; MPN 0402 100nF 6.3V X5R
C1305, C1306: 4.7uF; C_0402_1005Metric; MPN 0402 4.7uF 10V X5R
C1311, C1314: 1uF; C_0402_1005Metric; MPN 0402 1uF 6.3V X5R
C1312, C1313: 15pF; C_0402_1005Metric; MPN 0402 15pF 50V C0G
FB1301: 120R@100MHz; L_0603_1608Metric; MPN BLM18PG121SN1D
J1301: RJ45 GbE; RJ45_Hanrun_HR911130C_MagJack; MPN HR911130C; LCSC C50933
L1301: 2.2uH; L_1008_2520Metric; MPN MWSA2520S-2R2MT (2.2uH 1.5A)
Q1301: BSS138; SOT-23; MPN BSS138; LCSC C52895
R1301, R1302: 22R; R_0402_1005Metric; MPN 0402 22R 1%
R1303: 2.49k; R_0402_1005Metric; MPN 0402 2.49k 1%
R1304: 1.5k; R_0402_1005Metric; MPN 0402 1.5k 1%
R1305: 10k; R_0402_1005Metric; MPN 0402 10k 1%
R1306: 100k; R_0402_1005Metric; MPN 0402 100k 1%
R1307, R1308, R1309, R1310: 4.7k; R_0402_1005Metric; MPN 0402 4.7k 1%
R1311, R1312: 510R; R_0402_1005Metric; MPN 0402 510R 1%
U1301: RTL8211F-CG; WQFN-40-1EP_5x5mm_P0.4mm; MPN RTL8211F-CG; LCSC C187932
Y1301: 25MHz; Crystal_SMD_3225-4Pin_3.2x2.5mm; MPN X322525MOB4SI (25MHz 20pF); LCSC C9006

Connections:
ETH_CT_A: C1315.1, J1301.P1 (CT_A)
ETH_CT_B: C1316.1, J1301.P10 (CT_B)
ETH_LED_G_A: J1301.11 (LED_G_A), R1311.2
ETH_LED_Y_A: J1301.13 (LED_Y_A), R1312.2
ETH_MDC: U1301.13 (MDC); also elsewhere on the board
ETH_MDI0_N: J1301.P3 (MDI0-), U1301.2 (MDI0-)
ETH_MDI0_P: J1301.P2 (MDI0+), U1301.1 (MDI0+)
ETH_MDI1_N: J1301.P7 (MDI1-), U1301.5 (MDI1-)
ETH_MDI1_P: J1301.P4 (MDI1+), U1301.4 (MDI1+)
ETH_MDI2_N: J1301.P6 (MDI2-), U1301.7 (MDI2-)
ETH_MDI2_P: J1301.P5 (MDI2+), U1301.6 (MDI2+)
ETH_MDI3_N: J1301.P9 (MDI3-), U1301.10 (MDI3-)
ETH_MDI3_P: J1301.P8 (MDI3+), U1301.9 (MDI3+)
ETH_MDIO: R1304.1, U1301.14 (MDIO); also elsewhere on the board
GND: C1301.2, C1302.2, C1303.2, C1304.2, C1305.2, C1306.2, C1307.2, C1308.2, C1309.2, C1310.2, C1311.2, C1312.2, C1313.2, C1314.2, C1315.2, C1316.2, J1301.12 (LED_G_K), J1301.SHIELD0 (SHIELD), J1301.SHIELD1 (SHIELD), Q1301.2 (S), R1303.2, R1306.2, R1308.2, R1309.2, U1301.41 (EPAD), Y1301.2 (G), Y1301.4 (G); also elsewhere on the board
PHY_INT_L: R1307.1, U1301.31 (INTB/PMEB); also elsewhere on the board
PHY_LED0: R1308.1, U1301.32 (LED0/CFG_EXT)
PHY_LED1: R1309.1, R1311.1, U1301.33 (LED1/CFG_LDO0)
PHY_LED2: J1301.14 (LED_Y_K), R1310.1, U1301.34 (LED2/CFG_LDO1)
PHY_REG_OUT: L1301.1, U1301.30 (REG_OUT)
PHY_RSET: R1303.1, U1301.39 (RSET)
PHY_RST_GPIO: Q1301.1 (G), R1306.1; also elsewhere on the board
PHY_RST_L: C1314.1, Q1301.3 (D), R1305.1, U1301.12 (PHYRSTB)
PHY_XI: C1312.1, U1301.36 (XTAL_IN), Y1301.1
PHY_XO: C1313.1, U1301.37 (XTAL_OUT), Y1301.3
RGMII_RXC: R1302.2; also elsewhere on the board
RGMII_RXCTL: U1301.26 (RXCTL/PHYAD2); also elsewhere on the board
RGMII_RXC_PHY: R1302.1, U1301.27 (RXC/PHYAD1)
RGMII_RXD0: U1301.25 (RXD0/RXDLY); also elsewhere on the board
RGMII_RXD1: U1301.24 (RXD1/TXDLY); also elsewhere on the board
RGMII_RXD2: U1301.23 (RXD2/PLLOFF); also elsewhere on the board
RGMII_RXD3: U1301.22 (RXD3/PHYAD0); also elsewhere on the board
RGMII_TXC: R1301.2, U1301.20 (TXC)
RGMII_TXCTL: U1301.19 (TXCTL); also elsewhere on the board
RGMII_TXC_SOC: R1301.1; also elsewhere on the board
RGMII_TXD0: U1301.18 (TXD0); also elsewhere on the board
RGMII_TXD1: U1301.17 (TXD1); also elsewhere on the board
RGMII_TXD2: U1301.16 (TXD2); also elsewhere on the board
RGMII_TXD3: U1301.15 (TXD3); also elsewhere on the board
VCC3V3_PHY: C1301.1, C1302.1, C1303.1, C1304.1, FB1301.2, R1305.2, R1310.2, R1312.1, U1301.11 (AVDD33), U1301.29 (DVDD33), U1301.40 (AVDD33)
VCC_1V8_S3: C1311.1, R1304.2, R1307.2, U1301.28 (DVDD_RG); also elsewhere on the board
VCC_3V3_S3: FB1301.1; also elsewhere on the board
VDD10_PHY: C1305.1, C1306.1, C1307.1, C1308.1, C1309.1, C1310.1, L1301.2, U1301.3 (AVDD10), U1301.8 (AVDD10), U1301.21 (DVDD10), U1301.38 (AVDD10)

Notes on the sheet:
13_ethernet: Gigabit Ethernet (RTL8211F RGMII)
